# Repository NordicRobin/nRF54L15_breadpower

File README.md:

# nRF54L15_breadpower  

The nRF54L15_breadpower is a development board designed for breadboard prototyping with support for directly powering your breadboard project through USB-C, and battery power ing your final project with charging through USB-C.

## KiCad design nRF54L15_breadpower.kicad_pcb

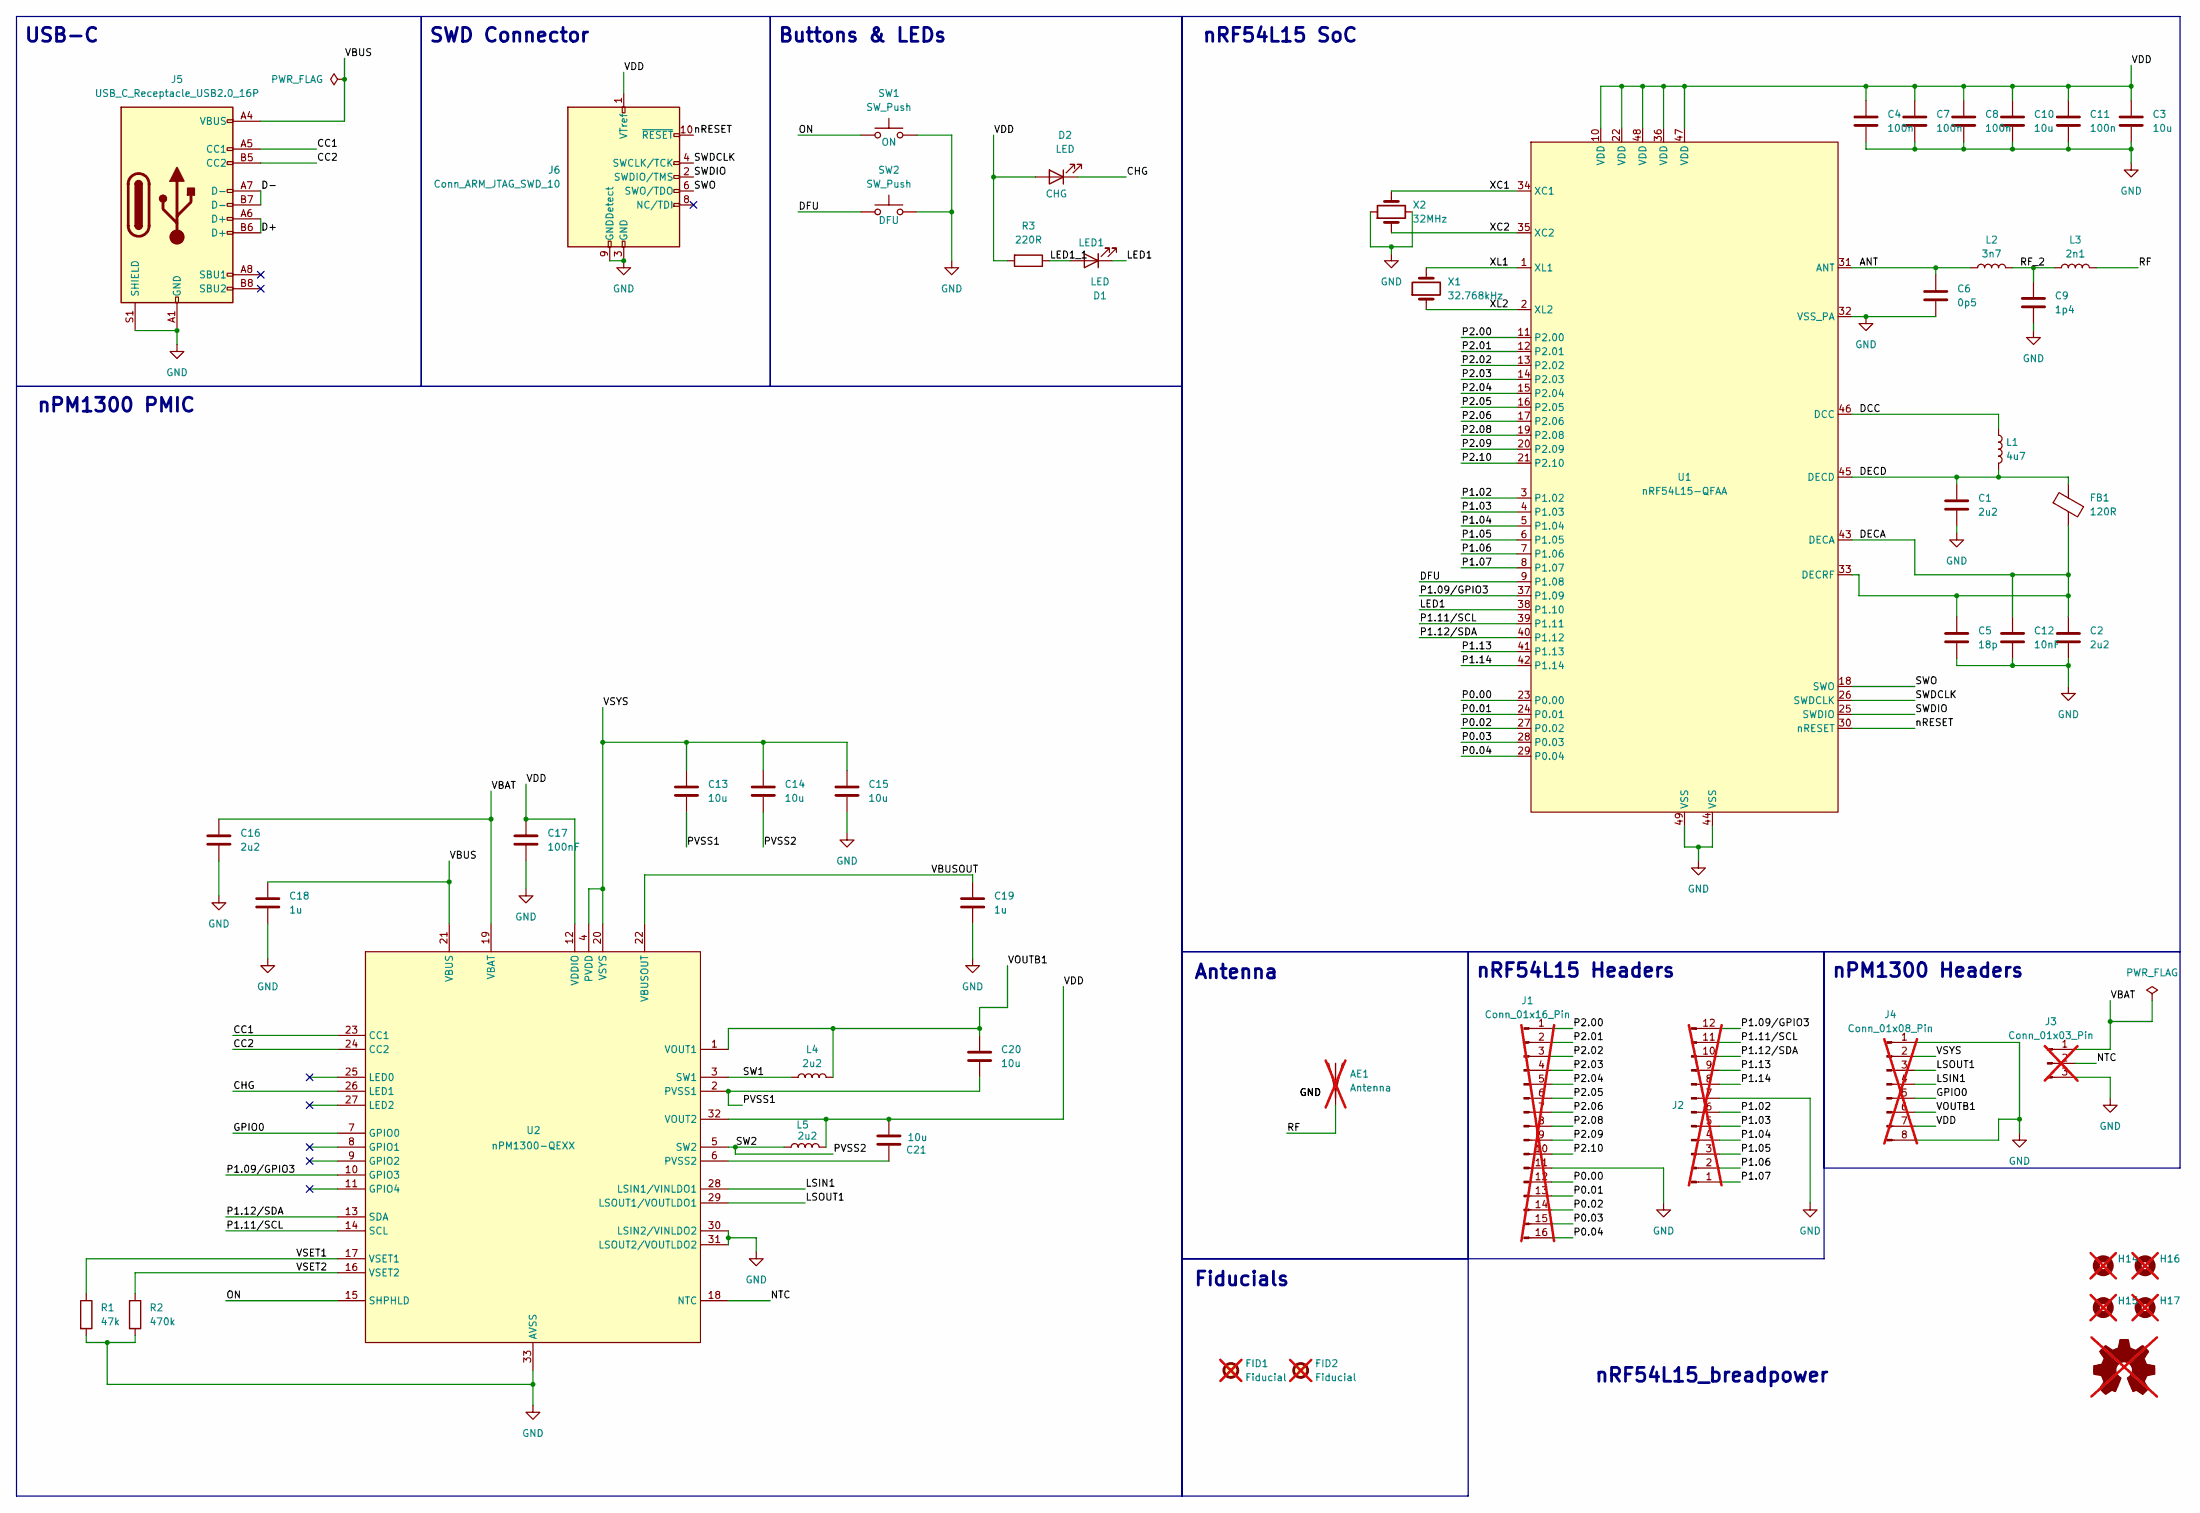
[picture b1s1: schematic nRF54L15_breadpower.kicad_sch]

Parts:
AE1: Antenna; Texas_SWRA117D_2.4GHz_Left; not fitted
C1, C2: 2u2; C_0201_0603Metric; Manufacturer Part Number GRM033D80E225ME47
C3, C10: 10u; C_0402_1005Metric; Manufacturer Part Number GRM155C80J106ME11D
C4, C7, C8, C11: 100n; C_0201_0603Metric; Manufacturer Part Number GRM033R61C104KE18D
C5: 18p; C_0201_0603Metric; Manufacturer Part Number GCM0335C1E180JA16J
C6: 0p5; C_0201_0603Metric; Manufacturer Part Number GJM0335C1ER50BB01J
C9: 1p4; C_0201_0603Metric; Manufacturer Part Number GJM0335C1E1R4WB01D
C12: 10nF; C_0201_0603Metric; Manufacturer Part Number GRT033R71A103KE01D
C13, C14, C15, C20, C21: 10u; L_0603_1608Metric; Manufacturer Part Number GRM188R61E106MA73D
C16: 2u2; L_0603_1608Metric; Manufacturer Part Number GRM188Z71C225KE43D
C17: 100nF; C_0201_0603Metric; Manufacturer Part Number GRM033R61E104KE14J
C18, C19: 1u; L_0603_1608Metric; Manufacturer Part Number GRM188R61A105KA61J
D1, D2: LED; LED_0603_1608Metric; Manufacturer Part Number IN-S63AT5A
FB1: 120R; L_0201_0603Metric; Manufacturer Part Number BLM03AG121SN1D
FID1, FID2: Fiducial; Fiducial_0.5mm_Mask1.5mm; not fitted
H14, H15, H16, H17: MountingHole; MountingHole_2.5mm; not fitted
J1: Conn_01x16_Pin; PinHeader_1x16_P2.54mm_Vertical; not fitted
J2: Conn_01x12_Pin; PinHeader_1x12_P2.54mm_Vertical; not fitted
J3: Conn_01x03_Pin; PinHeader_1x03_P2.54mm_Vertical; not fitted
J4: Conn_01x08_Pin; PinHeader_1x08_P2.54mm_Vertical; not fitted
J5: USB_C_Receptacle_USB2.0_16P; USB_C_Receptacle_HRO_TYPE-C-31-M-12; Manufacturer Part Number TYPE-C-31-M-12
J6: Conn_ARM_JTAG_SWD_10; PinHeader_2x05_P1.27mm_Vertical_SMD; Manufacturer Part Number FTSH-105-01-L-DV-K-TR
L1: 4u7; L_0603_1608Metric; Manufacturer Part Number MLZ1608M4R7WT000
L2: 3n7; L_0201_0603Metric; Manufacturer Part Number LQP03HQ3N7B02D
L3: 2n1; L_0201_0603Metric; Manufacturer Part Number LQP03HQ2N1W02D
L4, L5: 2u2; L_0805_2012Metric; Manufacturer Part Number MLZ2012M2R2HT000
R1: 47k; R_0201_0603Metric; Manufacturer Part Number RC0201FR-0747KL
R2: 470k; R_0201_0603Metric; Manufacturer Part Number RC0201FR-07470KL
R3: 220R; R_0201_0603Metric; Manufacturer Part Number AC0201FR-13220RL
SW1, SW2: SW_Push; SW_SPST_CK_RS282G05A3; Manufacturer Part Number RS-282G05A3-SM RT
SYM1: Logo_Open_Hardware_Small; not fitted
U1: nRF54L15-QFAA; QFN-48-1EP_6x6mm_P0.4mm_EP4.6x4.6mm; Manufacturer Part Number nRF54L15-QFAA
U2: nPM1300-QEXX; QFN-32-1EP_5x5mm_P0.5mm_EP3.6x3.6mm_ThermalVias; Manufacturer Part Number nPM1300-QEAA
X1: 32.768kHz; Crystal_SMD_2012-2Pin_2.0x1.2mm; Manufacturer Part Number 9HT11-32.768KDZC-T
X2: 32MHz; Crystal_SMD_2016-4Pin_2.0x1.6mm; Manufacturer Part Number MP06003

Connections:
/ANT: C6.1, L2.1, U1.31 (ANT)
/CC1: J5.A5 (CC1), U2.23 (CC1)
/CC2: J5.B5 (CC2), U2.24 (CC2)
/CHG: D2.1 (K), U2.26 (LED1)
/D+: J5.A6 (D+), J5.B6 (D+)
/D-: J5.A7 (D-), J5.B7 (D-)
/DCC: L1.1, U1.46 (DCC)
/DECA: C2.1, C5.1, C12.1, FB1.2, U1.33 (DECRF), U1.43 (DECA)
/DECD: C1.1, FB1.1, L1.2, U1.45 (DECD)
/DFU: SW2.1, U1.9 (P1.08)
/GPIO0: J4.5, U2.7 (GPIO0)
/LED1: D1.1 (K), U1.38 (P1.10)
/LED1_1: D1.2 (A), R3.1
/LSIN1: J4.4, U2.28 (LSIN1/VINLDO1)
/LSOUT1: J4.3, U2.29 (LSOUT1/VOUTLDO1)
/NTC: J3.2, U2.18 (NTC)
/ON: SW1.1, U2.15 (SHPHLD)
/P0.00: J1.12, U1.23 (P0.00)
/P0.01: J1.13, U1.24 (P0.01)
/P0.02: J1.14, U1.27 (P0.02)
/P0.03: J1.15, U1.28 (P0.03)
/P0.04: J1.16, U1.29 (P0.04)
/P1.02: J2.6, U1.3 (P1.02)
/P1.03: J2.5, U1.4 (P1.03)
/P1.04: J2.4, U1.5 (P1.04)
/P1.05: J2.3, U1.6 (P1.05)
/P1.06: J2.2, U1.7 (P1.06)
/P1.07: J2.1, U1.8 (P1.07)
/P1.09/GPIO3: J2.12, U1.37 (P1.09), U2.10 (GPIO3)
/P1.11/SCL: J2.11, U1.39 (P1.11), U2.14 (SCL)
/P1.12/SDA: J2.10, U1.40 (P1.12), U2.13 (SDA)
/P1.13: J2.9, U1.41 (P1.13)
/P1.14: J2.8, U1.42 (P1.14)
/P2.00: J1.1, U1.11 (P2.00)
/P2.01: J1.2, U1.12 (P2.01)
/P2.02: J1.3, U1.13 (P2.02)
/P2.03: J1.4, U1.14 (P2.03)
/P2.04: J1.5, U1.15 (P2.04)
/P2.05: J1.6, U1.16 (P2.05)
/P2.06: J1.7, U1.17 (P2.06)
/P2.08: J1.8, U1.19 (P2.08)
/P2.09: J1.9, U1.20 (P2.09)
/P2.10: J1.10, U1.21 (P2.10)
/PVSS1: C13.2, C20.2, U2.2 (PVSS1)
/PVSS2: C14.2, L5.1, U2.5 (SW2)
/RF: AE1.1 (A), L3.2
/RF_2: C9.1, L2.2, L3.1
/SW1: L4.1, U2.3 (SW1)
/SWDCLK: J6.4 (SWCLK/TCK), U1.26 (SWDCLK)
/SWDIO: J6.2 (SWDIO/TMS), U1.25 (SWDIO)
/SWO: J6.6 (SWO/TDO), U1.18 (SWO)
/VBAT: C16.1, J3.1, U2.19 (VBAT)
/VBUS: C18.1, J5.A4 (VBUS), J5.A9 (VBUS), J5.B4 (VBUS), J5.B9 (VBUS), U2.21 (VBUS)
/VBUSOUT: C19.1, U2.22 (VBUSOUT)
/VDD: C3.1, C4.1, C7.1, C8.1, C10.1, C11.1, C17.1, C21.1, D2.2 (A), J4.7, J6.1 (VTref), L5.2, R3.2, U1.10 (VDD), U1.22 (VDD), U1.36 (VDD), U1.47 (VDD), U1.48 (VDD), U2.12 (VDDIO), U2.32 (VOUT2)
/VOUTB1: C20.1, J4.6, L4.2, U2.1 (VOUT1)
/VSET1: R1.1, U2.17 (VSET1)
/VSET2: R2.1, U2.16 (VSET2)
/VSYS: C13.1, C14.1, C15.1, J4.2, U2.4 (PVDD), U2.20 (VSYS)
/XC1: U1.34 (XC1), X2.3
/XC2: U1.35 (XC2), X2.1
/XL1: U1.1 (XL1), X1.2
/XL2: U1.2 (XL2), X1.1
/nRESET: J6.10 (~RESET), U1.30 (nRESET)
GND: AE1.2 (GND), C1.2, C2.2, C3.2, C4.2, C5.2, C6.2, C7.2, C8.2, C9.2, C10.2, C11.2, C12.2, C15.2, C16.2, C17.2, C18.2, C19.2, J1.11, J2.7, J3.3, J4.1, J4.8, J5.A1 (GND), J5.A12 (GND), J5.B1 (GND), J5.B12 (GND), J5.S1 (SHIELD), J6.3 (GND), J6.5 (GND), J6.9 (GNDDetect), R1.2, R2.2, SW1.2, SW2.2, U1.32 (VSS_PA), U1.44 (VSS), U1.49 (VSS), U2.30 (LSIN2/VINLDO2), U2.31 (LSOUT2/VOUTLDO2), U2.33 (AVSS), X2.2, X2.4
unnamed: C21.2, U2.6 (PVSS2)

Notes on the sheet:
nPM1300 Headers
SWD Connector
nPM1300 PMIC
nRF54L15 Headers
Antenna
Buttons & LEDs
Fiducials
USB-C
nRF54L15_breadpower
nRF54L15 SoC

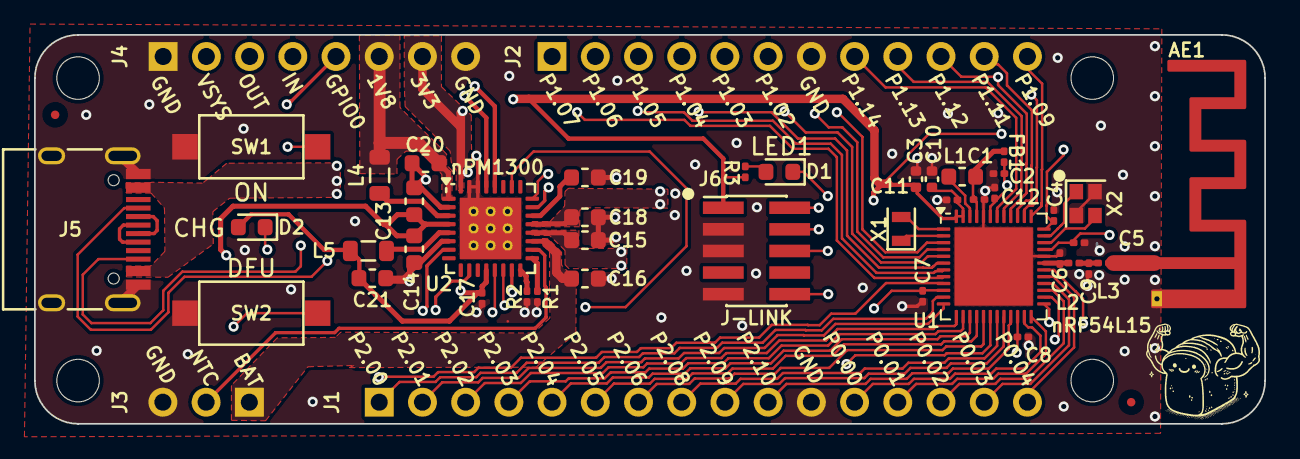
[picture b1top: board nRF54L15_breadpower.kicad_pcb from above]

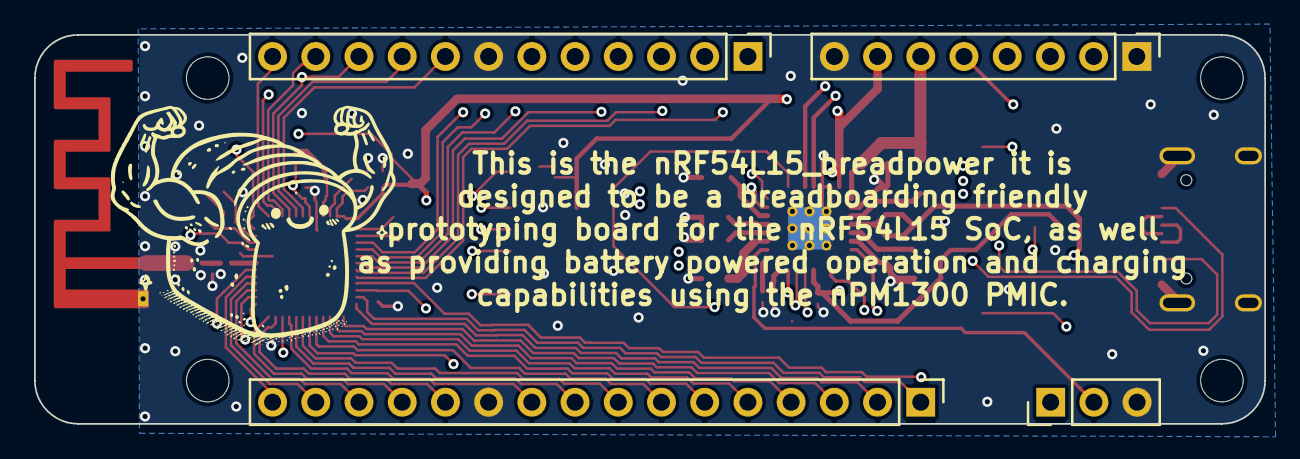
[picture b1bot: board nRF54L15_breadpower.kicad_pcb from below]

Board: 4 copper layers, 72.3 x 22.9 mm, 51 parts (4 on the bottom side), 66 nets.

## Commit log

2025-03-19 Add files via upload
    Initial commit
